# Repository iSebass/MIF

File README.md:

# MIF
Repositorio dedicado a la construccion de la tesis de la maestria en instrumentacion fisica

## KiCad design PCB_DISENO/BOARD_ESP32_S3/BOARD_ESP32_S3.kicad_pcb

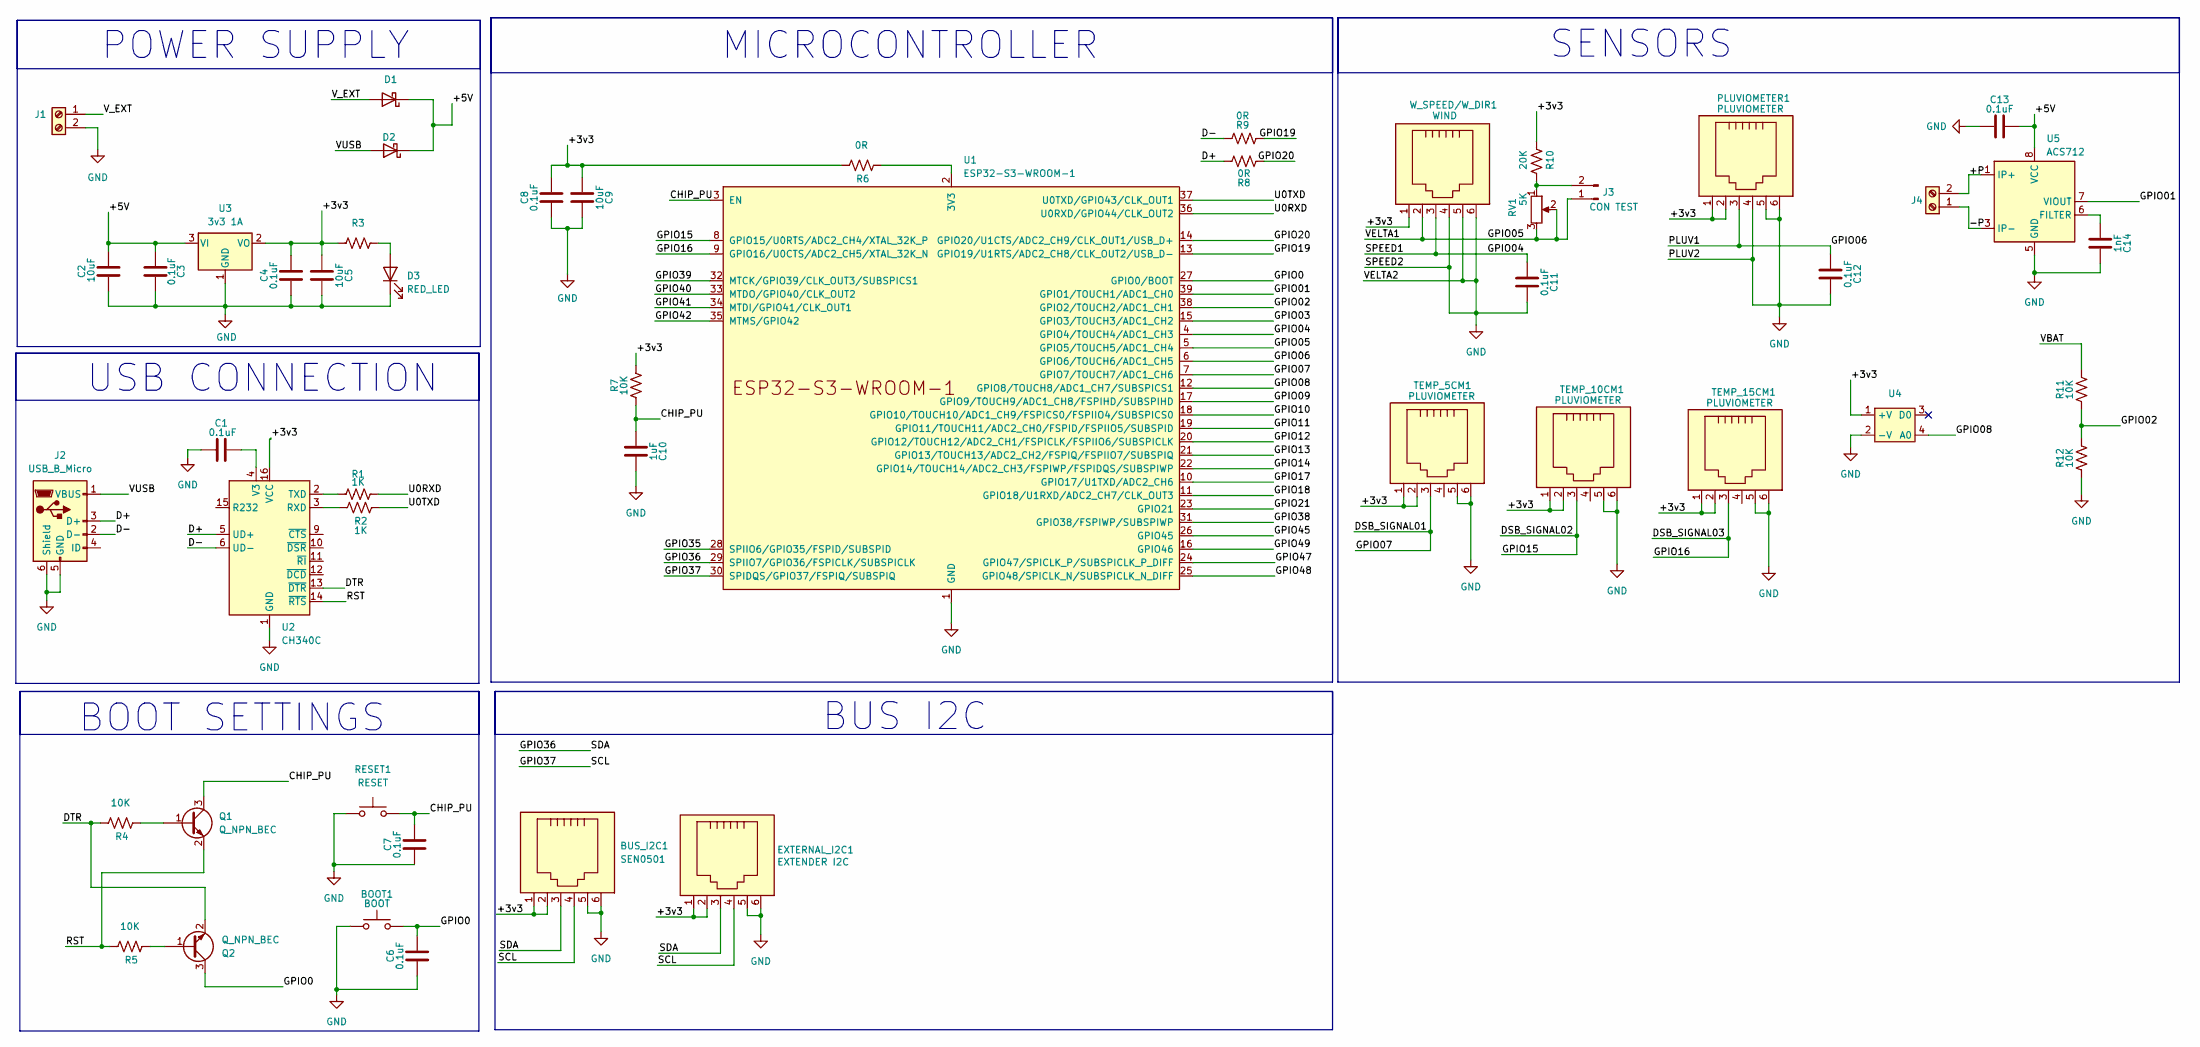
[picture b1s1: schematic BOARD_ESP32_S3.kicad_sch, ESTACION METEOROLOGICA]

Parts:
BOOT1: BOOT; SW_Tactile_SPST_NO_Straight_CK_PTS636Sx25SMTRLFS
BUS_I2C1: SEN0501; RJ25_Wayconn_MJEA-660X1_Horizontal
C1, C3, C4, C6, C7, C8, C11, C12, C13: 0.1uF; C_0805_2012Metric_Pad1.18x1.45mm_HandSolder
C2, C5, C9: 10uF; C_0805_2012Metric_Pad1.18x1.45mm_HandSolder
C10: 1uF; C_0805_2012Metric_Pad1.18x1.45mm_HandSolder
C14: 1nF; C_0805_2012Metric_Pad1.18x1.45mm_HandSolder
D1, D2: D_Schottky; D_SMA
D3: RED_LED; LED_0805_2012Metric
EXTERNAL_I2C1: EXTENDER I2C; RJ25_Wayconn_MJEA-660X1_Horizontal
J1, J4: INPUT_EXT; TerminalBlock_Altech_AK300-2_P5.00mm
J2: USB_B_Micro; USB_Micro-B_Molex_47346-0001
J3: CON TEST; PinHeader_1x02_P2.54mm_Vertical
PLUVIOMETER1: PLUVIOMETER; RJ25_Wayconn_MJEA-660X1_Horizontal
Q1, Q2: Q_NPN_BEC; SOT-23-3
R1, R2, R3: 1K; R_0805_2012Metric
R4, R5, R7, R11, R12: 10K; R_0805_2012Metric
R6, R8, R9: 0R; R_0805_2012Metric
R10: 20K; R_0805_2012Metric
RESET1: RESET; SW_Tactile_SPST_NO_Straight_CK_PTS636Sx25SMTRLFS
RV1: 5K; Potentiometer_Bourns_3266Y_Vertical
TEMP_5CM1, TEMP_10CM1, TEMP_15CM1: PLUVIOMETER; RJ25_Wayconn_MJEA-660X1_Horizontal
U1: ESP32-S3-WROOM-1
U2: CH340C; SOIC-16_3.9x9.9mm_P1.27mm
U3: 3v3 1A; SOT-223-3_TabPin2
U4: SIG2991
U5: ACS712; SOIC-8_3.9x4.9mm_P1.27mm
W_SPEED/W_DIR1: WIND; RJ25_Wayconn_MJEA-660X1_Horizontal

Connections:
/+3v3: BUS_I2C1.1, BUS_I2C1.2, C4.2, C5.2, C8.2, C9.2, EXTERNAL_I2C1.1, EXTERNAL_I2C1.2, PLUVIOMETER1.1, PLUVIOMETER1.2, R3.1, R6.1, R7.2, R10.2, TEMP_5CM1.1, TEMP_5CM1.2, TEMP_10CM1.1, TEMP_10CM1.2, TEMP_15CM1.1, TEMP_15CM1.2, U2.16 (VCC), U3.2 (VO), U4.1 (+V), W_SPEED/W_DIR1.1
/+5V: C2.2, C3.2, C13.2, D1.1 (K), D2.1 (K), U3.3 (VI), U5.8 (VCC)
/+P: J4.2, U5.1 (IP+), U5.2 (IP+)
/-P: J4.1, U5.3 (IP-), U5.4 (IP-)
/CHIP_PU: C7.2, C10.2, Q1.3 (C), R7.1, RESET1.2, U1.3 (EN)
/D+: J2.3 (D+), R8.2, U2.5 (UD+)
/D-: J2.2 (D-), R9.2, U2.6 (UD-)
/DSB_SIGNAL01: TEMP_5CM1.3, U1.7 (GPIO7/TOUCH7/ADC1_CH6)
/DSB_SIGNAL02: TEMP_10CM1.3, U1.8 (GPIO15/U0RTS/ADC2_CH4/XTAL_32K_P)
/DSB_SIGNAL03: TEMP_15CM1.3, U1.9 (GPIO16/U0CTS/ADC2_CH5/XTAL_32K_N)
/DTR: Q2.2 (E), R4.1, U2.13 (~DTR)
/GPIO0: BOOT1.2, C6.2, Q2.3 (C), U1.27 (GPIO0/BOOT)
/GPIO01: U1.39 (GPIO1/TOUCH1/ADC1_CH0), U5.7 (VIOUT)
/GPIO02: R11.1, R12.2, U1.38 (GPIO2/TOUCH2/ADC1_CH1)
/GPIO03: U1.15 (GPIO3/TOUCH3/ADC1_CH2)
/GPIO04: C11.1, U1.4 (GPIO4/TOUCH4/ADC1_CH3), W_SPEED/W_DIR1.3
/GPIO05: J3.1, RV1.2, RV1.3, U1.5 (GPIO5/TOUCH5/ADC1_CH4), W_SPEED/W_DIR1.2
/GPIO06: C12.1, PLUVIOMETER1.3, U1.6 (GPIO6/TOUCH6/ADC1_CH5)
/GPIO08: U1.12 (GPIO8/TOUCH8/ADC1_CH7/SUBSPICS1), U4.4 (A0)
/GPIO09: U1.17 (GPIO9/TOUCH9/ADC1_CH8/FSPIHD/SUBSPIHD)
/GPIO10: U1.18 (GPIO10/TOUCH10/ADC1_CH9/FSPICS0/FSPIIO4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)
/GPIO11: U1.19 (GPIO11/TOUCH11/ADC2_CH0/FSPID/FSPIIO5/S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)
/GPIO12: U1.20 (GPIO12/TOUCH12/ADC2_CH1/FSPICLK/FSPIIO6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)
/GPIO13: U1.21 (GPIO13/TOUCH13/ADC2_CH2/FSPIQ/FSPIIO7/S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)
/GPIO14: U1.22 (GPIO14/TOUCH14/ADC2_CH3/FSPIWP/FSPIDQS/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)
/GPIO17: U1.10 (GPIO17/U1TXD/ADC2_CH6)
/GPIO18: U1.11 (GPIO18/U1RXD/ADC2_CH7/CLK_OUT3)
/GPIO19: R9.1, U1.13 (GPIO19/U1RTS/ADC2_CH8/CLK_OUT2/USB_D-)
/GPIO20: R8.1, U1.14 (GPIO20/U1CTS/ADC2_CH9/CLK_OUT1/USB_D+)
/GPIO21: U1.23 (GPIO21)
/GPIO35: U1.28 (SPIIO6/GPIO35/FSPID/SUBSPID)
/GPIO36: BUS_I2C1.3, EXTERNAL_I2C1.3, U1.29 (SPIIO7/GPIO36/FSPICLK/SUBSPICLK)
/GPIO37: BUS_I2C1.4, EXTERNAL_I2C1.4, U1.30 (SPIDQS/GPIO37/FSPIQ/SUBSPIQ)
/GPIO38: U1.31 (GPIO38/FSPIWP/SUBSPIWP)
/GPIO39: U1.32 (MTCK/GPIO39/CLK_OUT3/SUBSPICS1)
/GPIO40: U1.33 (MTDO/GPIO40/CLK_OUT2)
/GPIO41: U1.34 (MTDI/GPIO41/CLK_OUT1)
/GPIO42: U1.35 (MTMS/GPIO42)
/GPIO45: U1.26 (GPIO45)
/GPIO47: U1.24 (GPIO47/SPICLK_P/SUBSPICLK_P_DIFF)
/GPIO48: U1.25 (GPIO48/SPICLK_N/SUBSPICLK_N_DIFF)
/GPIO49: U1.16 (GPIO46)
/RST: Q1.2 (E), R5.1, U2.14 (~RTS)
/U0RXD: R1.2, U1.36 (U0RXD/GPIO44/CLK_OUT2)
/U0TXD: R2.2, U1.37 (U0TXD/GPIO43/CLK_OUT1)
/VUSB: D2.2 (A), J2.1 (VBUS)
/V_EXT: D1.2 (A), J1.1
GND: BOOT1.1, BUS_I2C1.5, BUS_I2C1.6, C1.1, C2.1, C3.1, C4.1, C5.1, C6.1, C7.1, C8.1, C9.1, C10.1, C11.2, C12.2, C13.1, C14.1, D3.1 (K), EXTERNAL_I2C1.5, EXTERNAL_I2C1.6, J1.2, J2.5 (GND), J2.6 (Shield), PLUVIOMETER1.4, PLUVIOMETER1.5, PLUVIOMETER1.6, R12.1, RESET1.1, TEMP_5CM1.5, TEMP_5CM1.6, TEMP_10CM1.5, TEMP_10CM1.6, TEMP_15CM1.5, TEMP_15CM1.6, U1.1 (GND), U1.40 (GND), U1.41 (GND), U2.1 (GND), U3.1 (GND), U4.2 (-V), U5.5 (GND), W_SPEED/W_DIR1.4, W_SPEED/W_DIR1.5, W_SPEED/W_DIR1.6; also elsewhere on the board
unnamed: D3.2 (A), R3.2
unnamed: J3.2, R10.1, RV1.1
unnamed 50: R11.2; also elsewhere on the board
unnamed: Q1.1 (B), R4.2
unnamed: Q2.1 (B), R5.2
unnamed: R6.2, U1.2 (3V3)
unnamed: R2.1, U2.3 (RXD)
unnamed: R1.1, U2.2 (TXD)
unnamed: C1.2, U2.4 (V3)
unnamed: C14.2, U5.6 (FILTER)

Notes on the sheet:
BUS I2C
BOOT SETTINGS
SENSORS
USB CONNECTION
MICROCONTROLLER
POWER SUPPLY

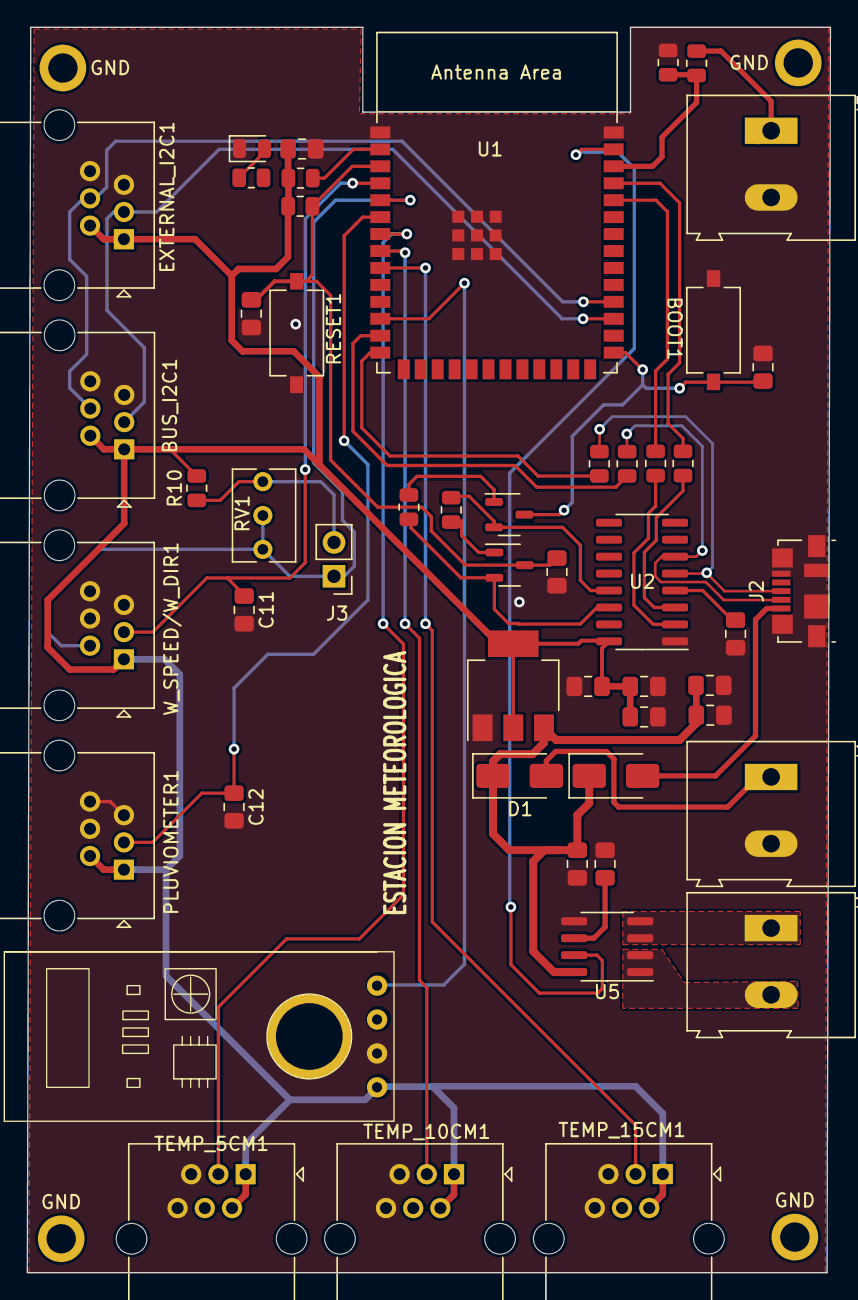
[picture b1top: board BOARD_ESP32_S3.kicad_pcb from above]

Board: 2 copper layers, 60.2 x 93.3 mm, 55 parts (0 on the bottom side), 38 nets.

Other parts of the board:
GND: MountingHole_2.2mm_M2_ISO7380_Pad
GND#2, GND#3, GND#4: MountingHole_2.2mm_M2_ISO7380_Pad
J5: INPUT_EXT; TerminalBlock_Altech_AK300-2_P5.00mm

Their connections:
GND: J5.2; also elsewhere on the board
unnamed 50: J5.1; also elsewhere on the board

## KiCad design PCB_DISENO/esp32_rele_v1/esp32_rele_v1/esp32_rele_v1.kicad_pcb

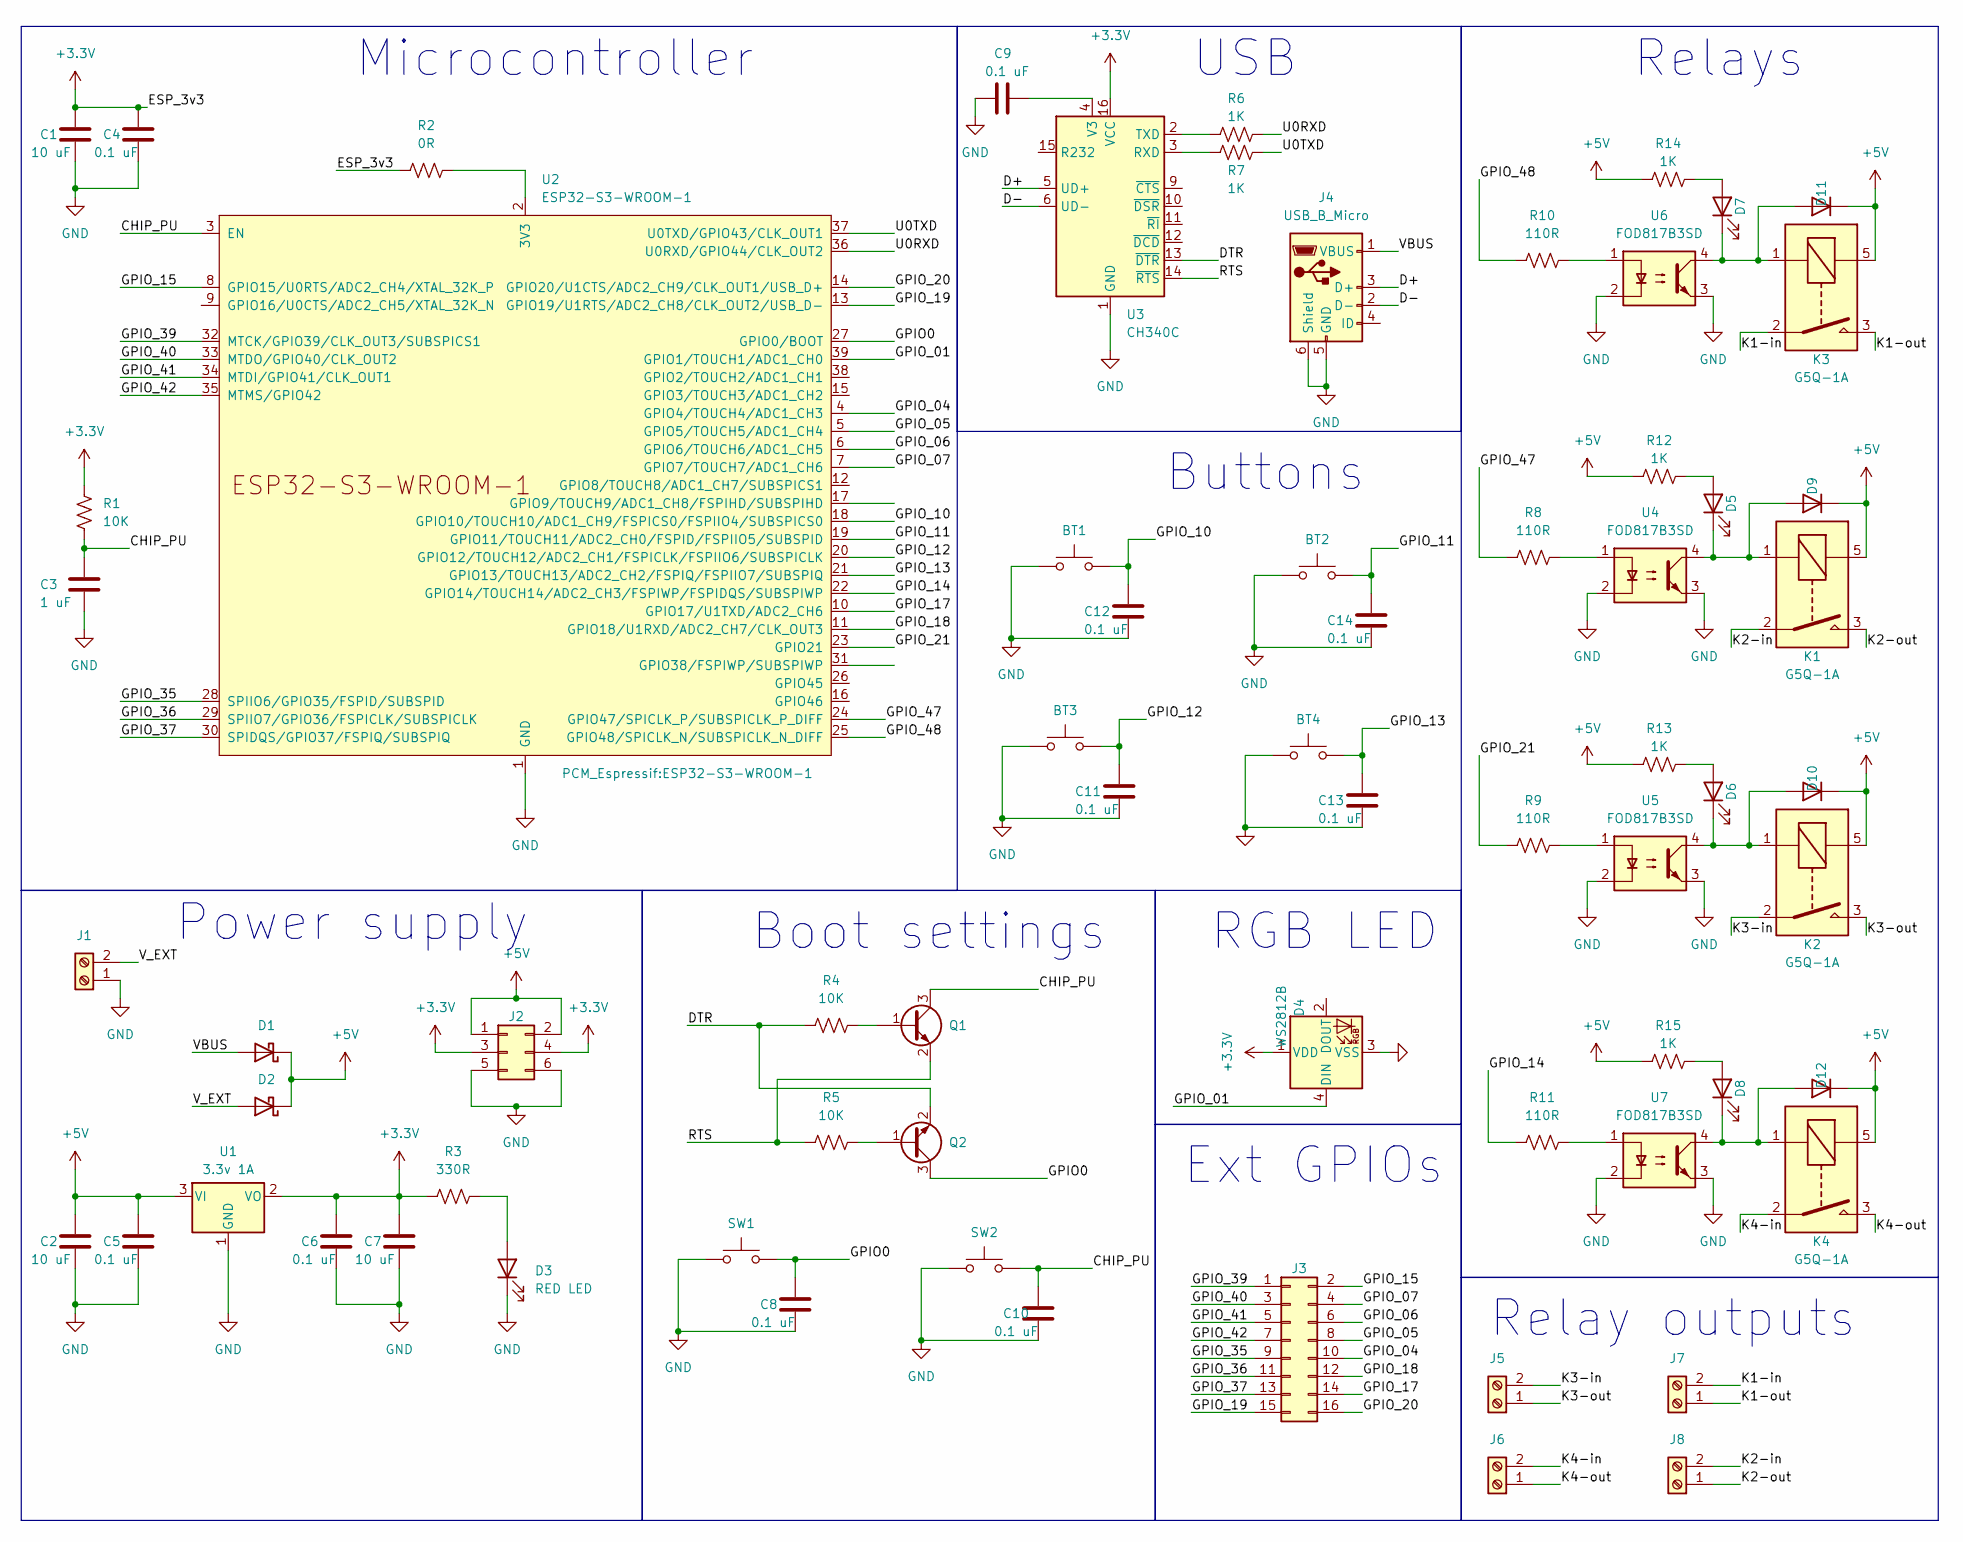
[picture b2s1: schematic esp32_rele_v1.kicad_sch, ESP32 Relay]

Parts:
BT1, BT2, BT3, BT4: SW_Push; SW_Tactile_SPST_NO_Straight_CK_PTS636Sx25SMTRLFS
C1, C2, C7: 10 uF; C_1206_3216Metric_Pad1.33x1.80mm_HandSolder
C3: 1 uF; C_1206_3216Metric_Pad1.33x1.80mm_HandSolder
C4, C5, C6, C8, C9, C10, C11, C12, C13, C14: 0.1 uF; C_0603_1608Metric_Pad1.08x0.95mm_HandSolder
D1, D2: D_Schottky; D_SMA
D3: RED LED; LED_1206_3216Metric
D4: WS2812B; LED_WS2812B_PLCC4_5.0x5.0mm_P3.2mm
D5, D6, D7, D8: Green LED; LED_1206_3216Metric
D9, D10, D11, D12: NRVA4007T3G; D_SMA
J1, J5, J6, J7, J8: Screw_Terminal_01x02; TerminalBlock_Phoenix_MKDS-1,5-2_1x02_P5.00mm_Horizontal
J2: Conn_02x03_Odd_Even; PinHeader_2x03_P2.54mm_Vertical_SMD
J3: Conn_02x08_Odd_Even; PinHeader_2x08_P2.54mm_Vertical_SMD
J4: USB_B_Micro; USB_Micro-B_Molex_47346-0001
K1, K2, K3, K4: G5Q-1A; Relay_SPST_Omron-G5Q-1A
Q1, Q2: Q_NPN_BEC; SOT-23-3
R1, R4, R5: 10K; R_1206_3216Metric
R2: 0R; R_1206_3216Metric
R3: 330R; R_1206_3216Metric
R6, R7, R12, R13, R14, R15: 1K; R_1206_3216Metric
R8, R9, R10, R11: 110R; R_1206_3216Metric
SW1, SW2: SW_Push; SW_Tactile_SPST_NO_Straight_CK_PTS636Sx25SMTRLFS
U1: 3.3v 1A; SOT-223-3_TabPin2
U2: ESP32-S3-WROOM-1
U3: CH340C; SOIC-16_3.9x9.9mm_P1.27mm
U4, U5, U6, U7: FOD817B3SD; SMDIP-4_W9.53mm

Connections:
+3.3V: C1.1, C4.1, C6.1, C7.1, D4.1 (VDD), J2.3, J2.4, R1.2, R2.1, R3.1, U1.2 (VO), U3.16 (VCC)
+5V: C2.1, C5.1, D1.1 (K), D2.1 (K), D9.1 (K), D10.1 (K), D11.1 (K), D12.1 (K), J2.1, J2.2, K1.5, K2.5, K3.5, K4.5, R12.1, R13.1, R14.1, R15.1, U1.3 (VI)
/CHIP_PU: C3.1, C10.1, Q1.3 (C), R1.1, SW2.2, U2.3 (EN)
/D+: J4.3 (D+), U3.5 (UD+)
/D-: J4.2 (D-), U3.6 (UD-)
/DTR: Q2.2 (E), R4.1, U3.13 (~DTR)
/GPIO0: C8.1, Q2.3 (C), SW1.2, U2.27 (GPIO0/BOOT)
/GPIO_01: D4.4 (DIN), U2.39 (GPIO1/TOUCH1/ADC1_CH0)
/GPIO_04: J3.10, U2.4 (GPIO4/TOUCH4/ADC1_CH3)
/GPIO_05: J3.8, U2.5 (GPIO5/TOUCH5/ADC1_CH4)
/GPIO_06: J3.6, U2.6 (GPIO6/TOUCH6/ADC1_CH5)
/GPIO_07: J3.4, U2.7 (GPIO7/TOUCH7/ADC1_CH6)
/GPIO_10: BT1.2, C12.1, U2.18 (GPIO10/TOUCH10/ADC1_CH9/FSPICS0/FSPIIO4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)
/GPIO_11: BT2.2, C14.1, U2.19 (GPIO11/TOUCH11/ADC2_CH0/FSPID/FSPIIO5/S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)
/GPIO_12: BT3.2, C11.1, U2.20 (GPIO12/TOUCH12/ADC2_CH1/FSPICLK/FSPIIO6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)
/GPIO_13: BT4.2, C13.1, U2.21 (GPIO13/TOUCH13/ADC2_CH2/FSPIQ/FSPIIO7/S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)
/GPIO_14: R11.1, U2.22 (GPIO14/TOUCH14/ADC2_CH3/FSPIWP/FSPIDQS/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)
/GPIO_15: J3.2, U2.8 (GPIO15/U0RTS/ADC2_CH4/XTAL_32K_P)
/GPIO_17: J3.14, U2.10 (GPIO17/U1TXD/ADC2_CH6)
/GPIO_18: J3.12, U2.11 (GPIO18/U1RXD/ADC2_CH7/CLK_OUT3)
/GPIO_19: J3.15, U2.13 (GPIO19/U1RTS/ADC2_CH8/CLK_OUT2/USB_D-)
/GPIO_20: J3.16, U2.14 (GPIO20/U1CTS/ADC2_CH9/CLK_OUT1/USB_D+)
/GPIO_21: R9.1, U2.23 (GPIO21)
/GPIO_35: J3.9, U2.28 (SPIIO6/GPIO35/FSPID/SUBSPID)
/GPIO_36: J3.11, U2.29 (SPIIO7/GPIO36/FSPICLK/SUBSPICLK)
/GPIO_37: J3.13, U2.30 (SPIDQS/GPIO37/FSPIQ/SUBSPIQ)
/GPIO_39: J3.1, U2.32 (MTCK/GPIO39/CLK_OUT3/SUBSPICS1)
/GPIO_40: J3.3, U2.33 (MTDO/GPIO40/CLK_OUT2)
/GPIO_41: J3.5, U2.34 (MTDI/GPIO41/CLK_OUT1)
/GPIO_42: J3.7, U2.35 (MTMS/GPIO42)
/GPIO_47: R8.1, U2.24 (GPIO47/SPICLK_P/SUBSPICLK_P_DIFF)
/GPIO_48: R10.1, U2.25 (GPIO48/SPICLK_N/SUBSPICLK_N_DIFF)
/K1-in: J7.2, K3.2
/K1-out: J7.1, K3.3
/K2-in: J8.2, K1.2
/K2-out: J8.1, K1.3
/K3-in: J5.2, K2.2
/K3-out: J5.1, K2.3
/K4-in: J6.2, K4.2
/K4-out: J6.1, K4.3
/RTS: Q1.2 (E), R5.1, U3.14 (~RTS)
/U0RXD: R6.2, U2.36 (U0RXD/GPIO44/CLK_OUT2)
/U0TXD: R7.2, U2.37 (U0TXD/GPIO43/CLK_OUT1)
/VBUS: D1.2 (A), J4.1 (VBUS)
/V_EXT: D2.2 (A), J1.2
GND: BT1.1, BT2.1, BT3.1, BT4.1, C1.2, C2.2, C3.2, C4.2, C5.2, C6.2, C7.2, C8.2, C9.2, C10.2, C11.2, C12.2, C13.2, C14.2, D3.1 (K), D4.3 (VSS), J1.1, J2.5, J2.6, J4.5 (GND), J4.6 (Shield), SW1.1, SW2.1, U1.1 (GND), U2.1 (GND), U2.40 (GND), U2.41 (GND), U3.1 (GND), U4.2, U4.3, U5.2, U5.3, U6.2, U6.3, U7.2, U7.3; also elsewhere on the board
unnamed 46: D3.2 (A), R3.2; also elsewhere on the board
unnamed: D5.2 (A), R12.2
unnamed: D5.1 (K), D9.2 (A), K1.1, U4.4
unnamed: D6.2 (A), R13.2
unnamed: D7.2 (A), R14.2
unnamed: D8.2 (A), R15.2
unnamed: D6.1 (K), D10.2 (A), K2.1, U5.4
unnamed: D7.1 (K), D11.2 (A), K3.1, U6.4
unnamed: D8.1 (K), D12.2 (A), K4.1, U7.4
unnamed: Q1.1 (B), R4.2
unnamed: Q2.1 (B), R5.2
unnamed: R8.2, U4.1
unnamed: R9.2, U5.1
unnamed: R10.2, U6.1
unnamed: R11.2, U7.1
unnamed: R2.2, U2.2 (3V3)
unnamed: R7.1, U3.3 (RXD)
unnamed: R6.1, U3.2 (TXD)
unnamed: C9.1, U3.4 (V3)

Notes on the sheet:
Relays
Buttons
Microcontroller
USB
Boot settings
Relay outputs
RGB LED
Ext GPIOs
Power supply

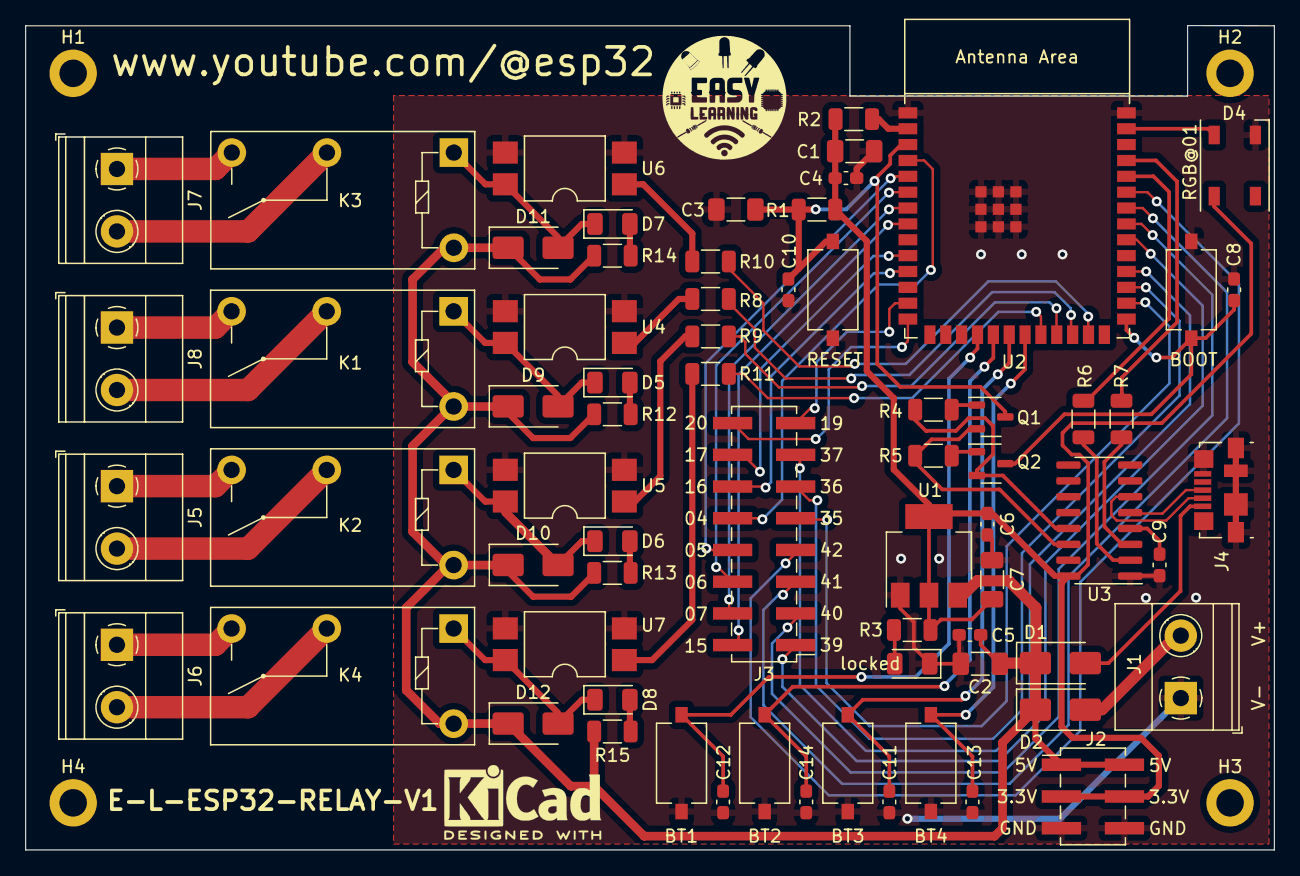
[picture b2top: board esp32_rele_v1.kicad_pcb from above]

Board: 2 copper layers, 100.0 x 66.0 mm, 72 parts (0 on the bottom side), 65 nets.

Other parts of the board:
H1, H2, H3, H4: MountingHole_2.2mm_M2_DIN965_Pad
locked: RED LED; LED_1206_3216Metric

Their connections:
GND: locked.1 (K); also elsewhere on the board
unnamed 46: locked.2 (A); also elsewhere on the board

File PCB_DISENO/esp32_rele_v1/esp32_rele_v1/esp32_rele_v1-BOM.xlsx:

Item | Qty | Reference(s) | Value | LibPart | Footprint | Datasheet | DNP | Description | Manufacturer | Price | Product Number
1 | 6 | BT1, BT2, BT3, BT4, SW1, SW2 | SW_Push | Switch:SW_Push | Button_Switch_SMD:SW_Tactile_SPST_NO_Straight_CK_PTS636Sx25SMTRLFS | https://www.ckswitches.com/media/2779/pts636.pdf |  | Tactile Switch SPST-NO Top Actuated Surface Mount | C&K | 0.15 | PTS636 SK25 SMTR LFS
2 | 3 | C1, C2, C7 | 10 uF | Device:C | Capacitor_SMD:C_1206_3216Metric_Pad1.33x1.80mm_HandSolder | https://connect.kemet.com:7667/gateway/IntelliData-Component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 |  | CAP CER 10UF 25V X5R 1206 | KEMET | 0.27 | C1206C106M3PAC7800
3 | 1 | C3 | 1 uF | Device:C | Capacitor_SMD:C_1206_3216Metric_Pad1.33x1.80mm_HandSolder | https://connect.kemet.com:7667/gateway/IntelliData-Component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 |  | 1 ÂµF Â±20% 16V Ceramic Capacitor X7R 1206 (3216 Metric) | KEMET | 0.17 | C1206C105M4RAC7800
4 | 10 | C4, C5, C6, C8, C9, C10, C11, C12, C13, C14 | 0.1 uF | Device:C | Capacitor_SMD:C_0603_1608Metric_Pad1.08x0.95mm_HandSolder | https://connect.kemet.com:7667/gateway/IntelliData-Component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 |  | CAP CER 0.1UF 50V X7R 0603 | KEMET | 0.11 | C0603C104K5RAC7867
5 | 2 | D1, D2 | D_Schottky | Device:D_Schottky | Diode_SMD:D_SMA | https://www.st.com/content/ccc/resource/technical/document/d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 |  | DIODE SCHOTTKY 30V 2A SMA | STMicroelectronics | 0.36 | STPS2L30A
6 | 1 | D3 | RED LED | Device:LED | LED_SMD:LED_1206_3216Metric | https://s3-us-west-2.amazonaws.com/catsy.557/Dialight_CBI_da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 |  | Red 635nm LED Indication - Discrete 2V 1206 (3216 Metric) | Dialight | 0.33 | 5988210107F
7 | 1 | D4 | WS2812B | LED:WS2812B | LED_SMD:LED_WS2812B_PLCC4_5.0x5.0mm_P3.2mm | https://cdn-shop.adafruit.com/datasheets/WS2812B.pdf |  | Addressable Lighting - LED Serial NRZ (Shift Register) Red, Green, Blue (RGB) | SparkFun Electronics | 0.57999999999999996 | COM-16347
8 | 4 | D5, D6, D7, D8 | Green LED | Device:LED | LED_SMD:LED_1206_3216Metric | https://s3-us-west-2.amazonaws.com/catsy.557/Dialight_CBI_da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 |  | Green 566nm LED Indication - Discrete 2V 1206 (3216 Metric) | Dialight | 0.32 | 5988270107F
9 | 4 | D9, D10, D11, D12 | NRVA4007T3G | Diode:MRA4007T3G | Diode_SMD:D_SMA | https://www.onsemi.com/pdf/datasheet/mra4003t3-d.pdf |  | Diode 1000 V 1A Surface Mount SMA | onsemi | 0.41 | NRVA4007T3G
10 | 5 | J1, J5, J6, J7, J8 | Screw_Terminal_01x02 | Connector:Screw_Terminal_01x02 | TerminalBlock_Phoenix:TerminalBlock_Phoenix_MKDS-1,5-2_1x02_P5.00mm_Horizontal | https://media.digikey.com/PDF/Data%20Sheets/Phoenix%20Contac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 |  | 2 Position Wire to Board Terminal Block Horizontal with Board 0.197" (5.00mm) T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 | Phoenix Contact | 1.26 | 1734656
11 | 1 | J2 | Conn_02x03_Odd_Even | Connector_Generic:Conn_02x03_Odd_Even | Connector_PinHeader_2.54mm:PinHeader_2x03_P2.54mm_Vertical_SMD | https://cdn.amphenol-cs.com/media/wysiwyg/files/drawing/54202.pdf |  | Connector Header Surface Mount 6 position 0.100" (2.54mm) | Amphenol ICC (FCI) | 0.45 | 54202-S0803LF
12 | 1 | J3 | Conn_02x08_Odd_Even | Connector_Generic:Conn_02x08_Odd_Even | Connector_PinHeader_2.54mm:PinHeader_2x08_P2.54mm_Vertical_SMD | https://cdn.amphenol-cs.com/media/wysiwyg/files/drawing/54202.pdf |  | Connector Header Surface Mount 16 position 0.100" (2.54mm) | Amphenol ICC (FCI) | 1.06 | 54202-G30-08
13 | 1 | J4 | USB_B_Micro | Connector:USB_B_Micro | Connector_USB:USB_Micro-B_Molex_47346-0001 | https://tools.molex.com/pdm_docs/sd/473460001_sd.pdf |  | CONN RCPT USB2.0 MICRO B SMD R/A | Molex | 1.17 | 473460001
14 | 4 | K1, K2, K3, K4 | G5Q-1A | Relay:G5Q-1A | Relay_THT:Relay_SPST_Omron-G5Q-1A | https://www.omron.com/ecb/products/pdf/en-g5q.pdf |  | General Purpose Relay SPST-NO (1 Form A) 5VDC Coil Through Hole | Omron Electronics Inc-EMC Div | 1.57 | G5Q-1A4 DC5
15 | 2 | Q1, Q2 | Q_NPN_BEC | Device:Q_NPN_BEC | Package_TO_SOT_SMD:SOT-23-3 | https://www.onsemi.com/pdf/datasheet/mmbt2222lt1-d.pdf |  | Bipolar (BJT) Transistor NPN 30 V 600 mA 250MHz 300 mW Surface Mount SOT-23-3 (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 | onsemi | 0.16 | MMBT2222LT1G
16 | 3 | R1, R4, R5 | 10K | Device:R_US | Resistor_SMD:R_1206_3216Metric | https://industrial.panasonic.com/ww/products/pt/general-purp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 |  | RES SMD 10K OHM 5% 1/4W 1206 | Panasonic Electronic Components | 0.12 | ERJ-8GEYJ103V
17 | 1 | R2 | 0R | Device:R_US | Resistor_SMD:R_1206_3216Metric | https://industrial.panasonic.com/ww/products/pt/general-purp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 |  | 0 Ohms Jumper Chip Resistor 1206 (3216 Metric) Automotive AEC-Q200 Thick Film | Panasonic Electronic Components | 0.14000000000000001 | ERJ-8GEY0R00V
18 | 1 | R3 | 330R | Device:R_US | Resistor_SMD:R_1206_3216Metric | https://industrial.panasonic.com/ww/products/pt/general-purp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 |  | RES SMD 330 OHM 5% 1/4W 1206 | Panasonic Electronic Components | 0.14000000000000001 | ERJ-8GEYJ331V
19 | 6 | R6, R7, R12, R13, R14, R15 | 1K | Device:R_US | Resistor_SMD:R_1206_3216Metric | https://industrial.panasonic.com/ww/products/pt/general-purp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 |  | RES SMD 1K OHM 5% 2/3W 1206 | Panasonic Electronic Components | 0.14000000000000001 | ERJ-P08J102V
20 | 4 | R8, R9, R10, R11 | 110R | Device:R_US | Resistor_SMD:R_1206_3216Metric | https://industrial.panasonic.com/ww/products/pt/general-purp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 |  | Â±5% 0.25W, 1/4W Chip Resistor 1206 (3216 Metric) Automotive AEC-Q200 Thick Film | Panasonic Electronic Components | 0.13 | ERJ-8GEYJ111V
21 | 1 | U1 | 3.3v 1A | Regulator_Linear:AZ1117-3.3 | Package_TO_SOT_SMD:SOT-223-3_TabPin2 | https://www.diodes.com/assets/Datasheets/AZ1117C.pdf |  | IC REG LINEAR 3.3V 1A SOT223 | Diodes Incorporated | 0.45 | AZ1117CH-3.3TRG1
22 | 1 | U2 | ESP32-S3-WROOM-1 | PCM_Espressif:ESP32-S3-WROOM-1 | PCM_Espressif:ESP32-S3-WROOM-1 | https://www.espressif.com/sites/default/files/documentation/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 |  | WiFi 802.11a/b/g/n, Bluetooth v5.0 Transceiver Module 2.4GHz PCB Trace | Espressif Systems | 3.35 | ESP32-S3-WROOM-1-N8R2
23 | 1 | U3 | CH340C | Interface_USB:CH340C | Package_SO:SOIC-16_3.9x9.9mm_P1.27mm | https://datasheet.lcsc.com/szlcsc/Jiangsu-Qin-Heng-CH340C_C8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 |  | USB to serial port chip | WCH | 0.73 | CH340C
24 | 4 | U4, U5, U6, U7 | FOD817B3SD | Isolator:LTV-817S | Package_DIP:SMDIP-4_W9.53mm | https://www.onsemi.com/pdf/datasheet/fod814-d.pdf |  | Optoisolator Transistor Output 5000Vrms 1 Channel 4-SMD | onsemi | 0.53 | FOD817B3SD

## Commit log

2023-12-26 Se agrega documento de plantilla de Trabajo de grado
2023-12-26 Se ajusta la problematica de la tesis con referencias y citas
2023-12-27 Se agregan elementos del primer capitulo
2024-01-12 Se agregan recursos del primer capitulo al documento
2024-02-08 Se ajusta PCB
2024-05-23 Se agregan elementos de maestria
